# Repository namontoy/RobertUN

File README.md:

# RobertUN
Exploration Rover, inspired by the NASA's rovers that are exploring Mars. Developed at Universidad Nacional de Colombia - Sede Medellín, with the financial support from a research project.

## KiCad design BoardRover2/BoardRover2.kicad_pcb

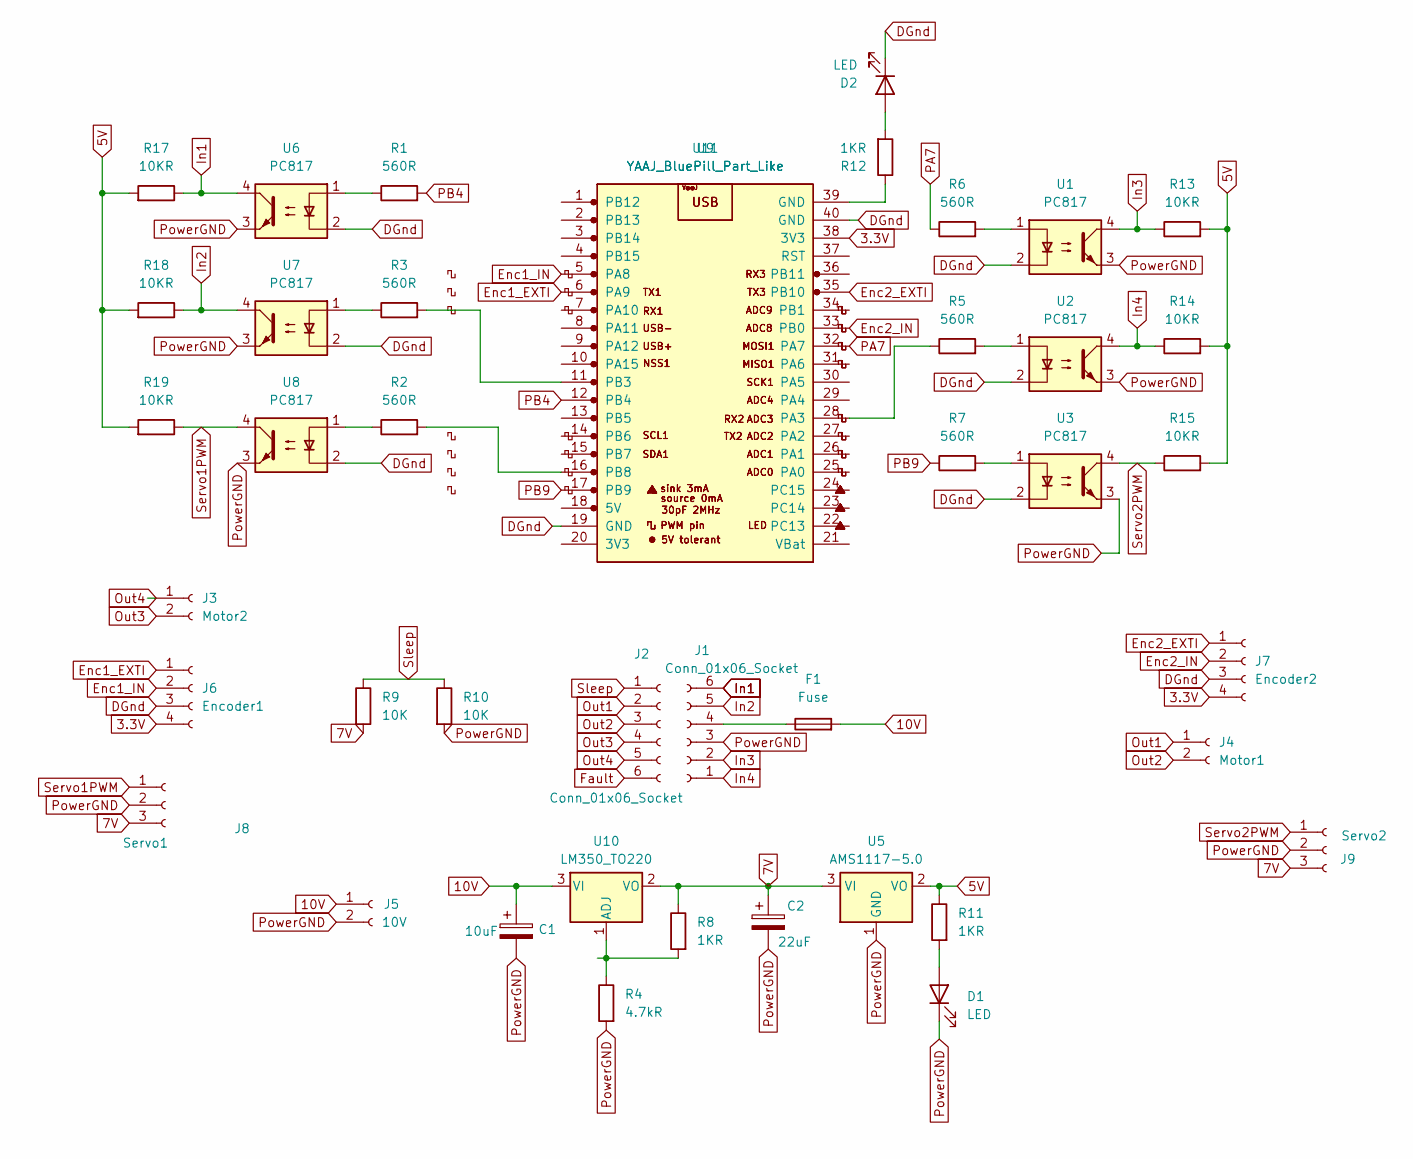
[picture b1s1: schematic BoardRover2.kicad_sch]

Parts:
C1: 10uF; C_1206_3216Metric
C2: 22uF; C_1206_3216Metric
D1, D2: LED; LED_D3.0mm_Clear
F1: Fuse; Fuse_1812_4532Metric
J1, J2: Conn_01x06_Socket; PinSocket_1x06_P2.54mm_Vertical
J3: Motor2; PhoenixContact_MSTBA_2,5_2-G-5,08_1x02_P5.08mm_Horizontal
J4: Motor1; PhoenixContact_MSTBA_2,5_2-G-5,08_1x02_P5.08mm_Horizontal
J5: 10V; PhoenixContact_MSTBA_2,5_2-G-5,08_1x02_P5.08mm_Horizontal
J6: Encoder1; JST_EH_S4B-EH_1x04_P2.50mm_Horizontal
J7: Encoder2; JST_EH_S4B-EH_1x04_P2.50mm_Horizontal
J8: Servo1; JST_EH_S3B-EH_1x03_P2.50mm_Horizontal
J9: Servo2; JST_EH_S3B-EH_1x03_P2.50mm_Horizontal
R1, R2, R3, R5, R6, R7: 560R; R_1206_3216Metric
R4: 4.7kR; R_1206_3216Metric
R8, R11, R12: 1KR; R_1206_3216Metric
R9, R10: 10K; R_1206_3216Metric
R13, R14, R15, R17, R18, R19: 10KR; R_1206_3216Metric
U1, U2, U3, U6, U7, U8: PC817; DIP-4_W7.62mm
U5: AMS1117-5.0; SOT-223-3_TabPin2
U9, U11: YAAJ_BluePill_Part_Like; PinSocket_1x20_P2.54mm_Vertical
U10: LM350_TO220; TO-220-3_Vertical

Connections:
3.3V: J6.4, J7.4, U11.38 (3V3)
5V: R11.1, R13.2, R14.2, R15.2, R17.2, R18.2, R19.2, U5.2 (VO)
7V: C2.1, J8.3, J9.3, R8.1, R9.2, U5.3 (VI), U10.2 (VO)
10V: C1.1, F1.2, J5.1, U10.3 (VI)
DGnd: D2.1 (K), J6.3, J7.3, U1.2, U2.2, U3.2, U6.2, U7.2, U8.2, U9.19 (GND), U11.40 (GND)
Enc1_EXTI: J6.1, U9.6 (PA9)
Enc1_IN: J6.2, U9.5 (PA8)
Enc2_EXTI: J7.1, U11.35 (PB10)
Enc2_IN: J7.2, U11.33 (PB0)
Fault: J2.6 (Fault)
In1: J1.6 (In1), R17.1, U6.4
In2: J1.5 (In2), R18.1, U7.4
In3: J1.2 (In3), R13.1, U1.4
In4: J1.1 (In4), R14.1, U2.4
unnamed: D1.2 (A), R11.2
unnamed: D2.2 (A), R12.2
unnamed: F1.1, J1.4 (MotorVCC)
unnamed: R1.1, U6.1
unnamed: R2.1, U8.1
unnamed: R3.1, U7.1
unnamed: R5.2, U2.1
unnamed: R6.2, U1.1
unnamed: R7.2, U3.1
unnamed: R12.1, U11.39 (GND)
unnamed: R3.2, U9.11 (PB3)
unnamed: R2.2, U9.16 (PB8)
unnamed: R4.1, R8.2, U10.1 (ADJ)
unnamed: R5.1, U11.28 (PA3)
Out1: J2.2 (Out1), J4.1
Out2: J2.3 (Out2), J4.2
Out3: J2.4 (Out3), J3.2
Out4: J2.5 (Out4), J3.1
PA7: R6.1, U11.32 (PA7)
PB4: R1.2, U9.12 (PB4)
PB9: R7.1, U9.17 (PB9)
PowerGND: C1.2, C2.2, D1.1 (K), J1.3 (MotorGND), J5.2, J8.2, J9.2, R4.2, R10.2, U1.3, U2.3, U3.3, U5.1 (GND), U6.3, U7.3, U8.3
Servo1PWM: J8.1, R19.1, U8.4
Servo2PWM: J9.1, R15.1, U3.4
Sleep: J2.1 (Sleep), R9.1, R10.1

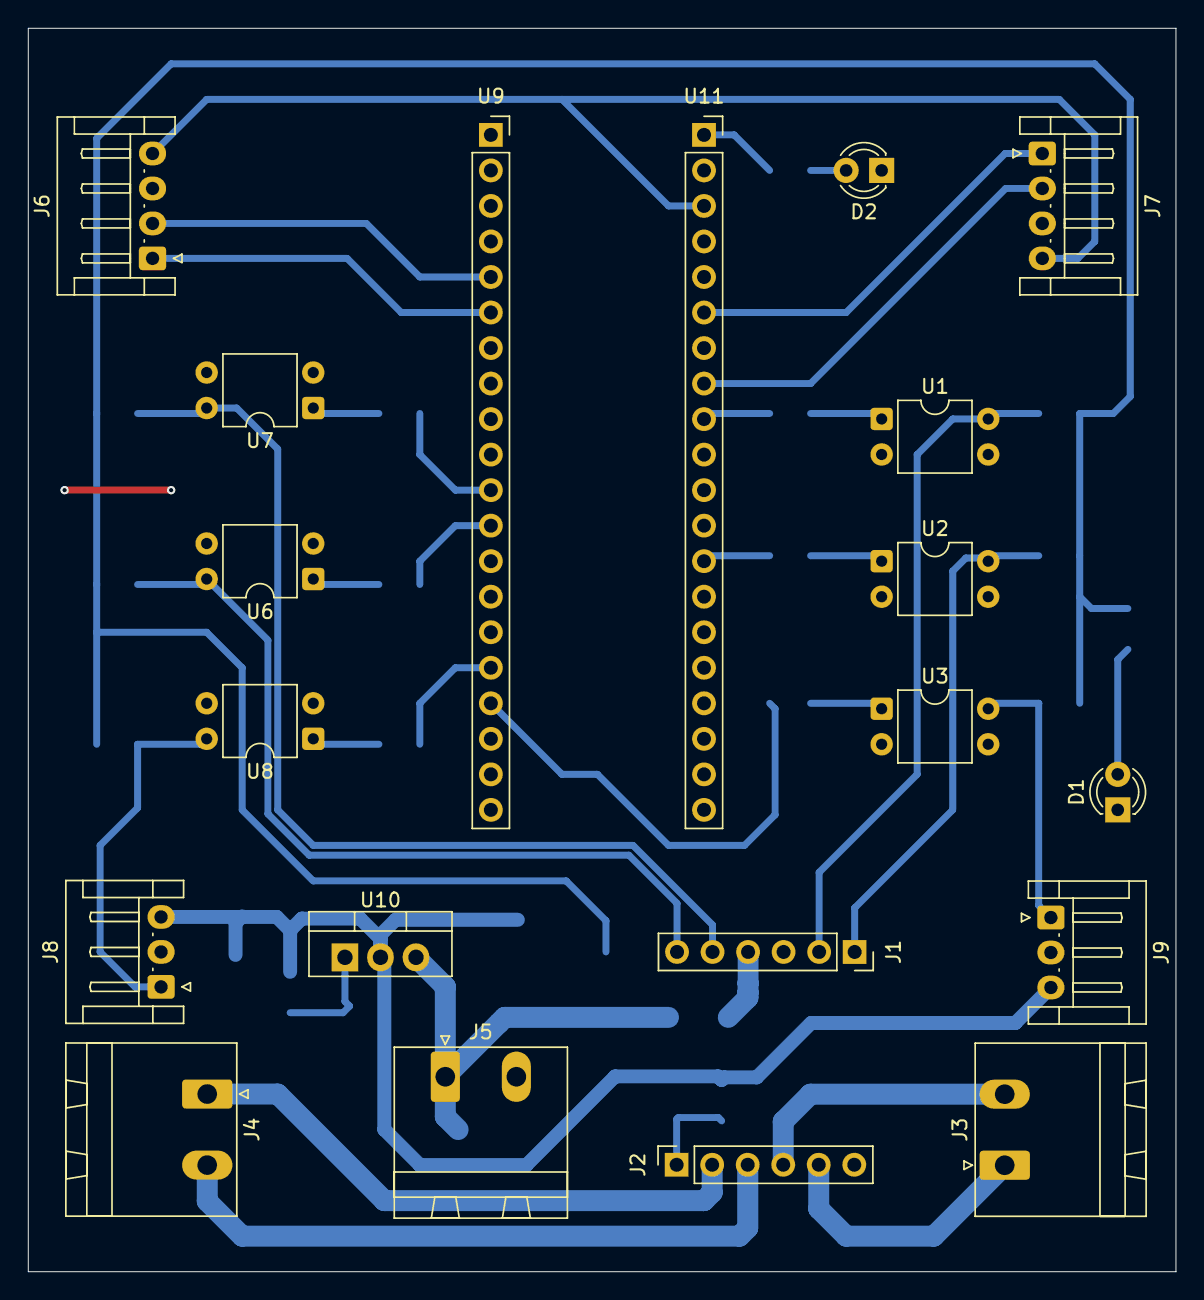
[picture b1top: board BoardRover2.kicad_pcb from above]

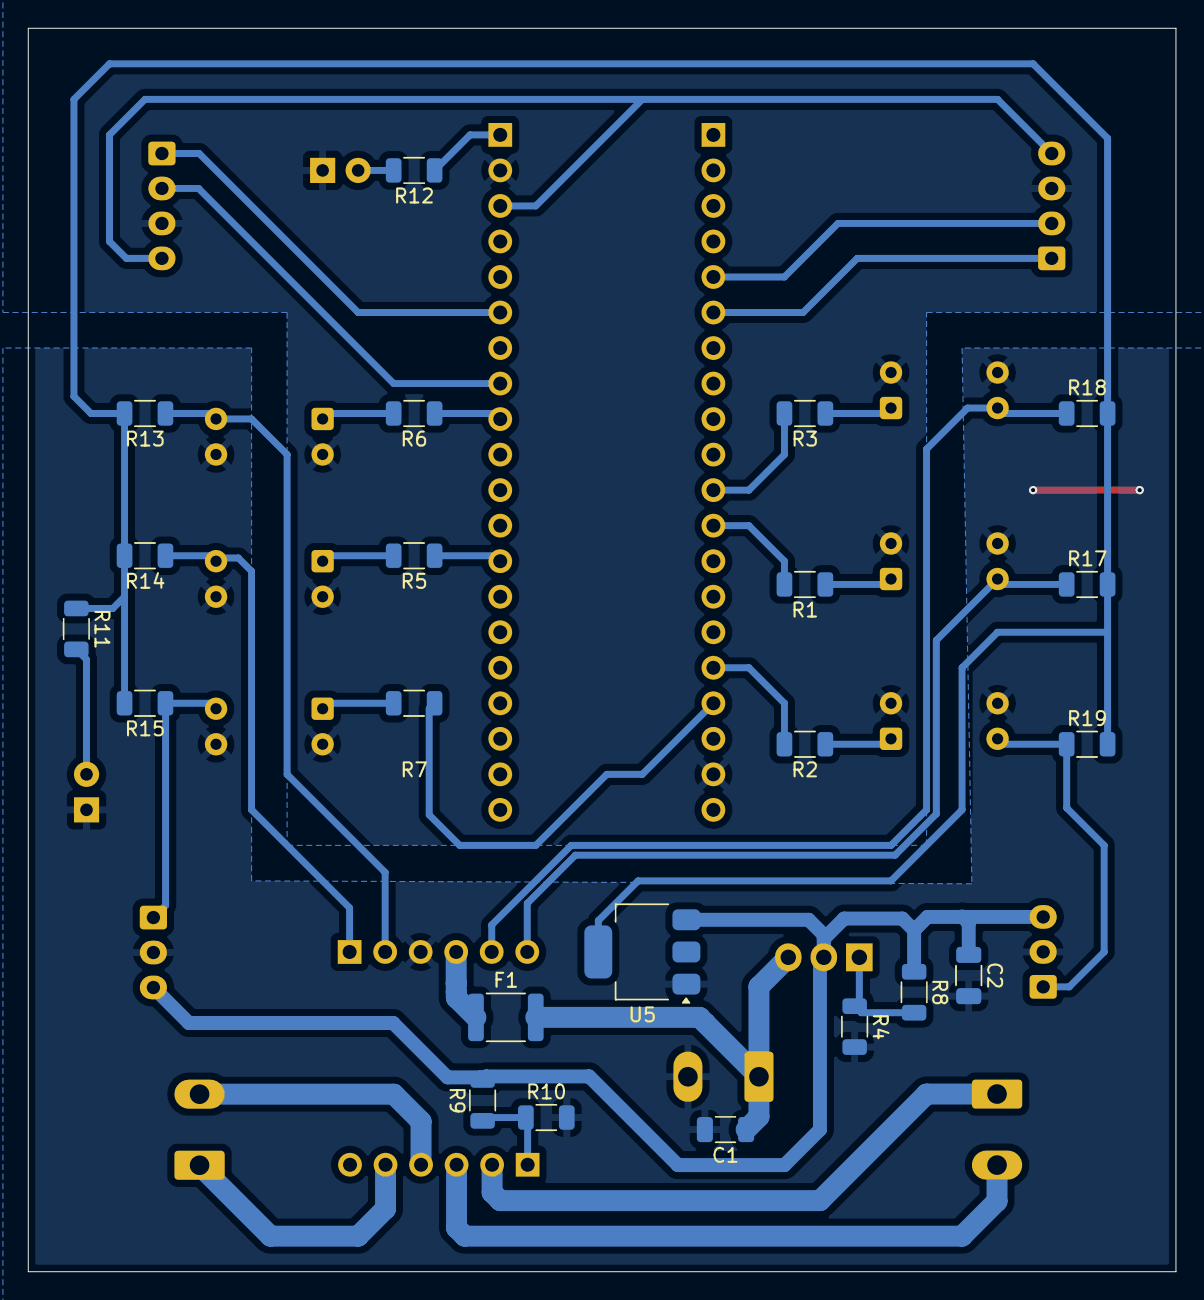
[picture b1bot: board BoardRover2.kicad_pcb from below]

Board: 2 copper layers, 82.1 x 88.9 mm, 42 parts (22 on the bottom side), 38 nets.

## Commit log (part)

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2025-11-19 Add files via upload - Jetson init
2025-11-19 add summary of additional programs used during Jetson Nano setup
2025-12-04 Create A_V dir and add Documentation
2025-12-04 Add install_yolo_deps.sh
2025-12-18 Board Kicad
2025-12-18 LED Y FUSIL
2025-12-18 revisado distancia pistas
2026-01-29 doble board y correxion
2026-02-14 info + storage bench
2026-02-14 creating a plan for the weeks
2026-02-17 Update2 plan.md
2026-02-21 ROS2 Humble setup + ros2_ws + /alive heartbeat node, also adding gitignore and checking docker install
2026-04-02 Add development environment context document for Dell, IsaacUN and Jetson setup
2026-04-02 Add initial development environment context - Dell laptop + Jetson setup (March 25, 2026)
2026-04-02 Add IsaacUN workstation configuration - Ubuntu 24.04, RTX 5080, ROS2 Jazzy, Isaac Sim 5.1.0 (March 30, 2026)
2026-04-02 Add CAN bus research document - Jetson Orin Nano hardware and software guide
2026-04-02 Network update - gigabit switch installed, static Ethernet IPs, DDS over wired (April 2, 2026)
2026-04-03 Add Dell laptop conda environments - ros2 (Humble) and ml (PyTorch+CUDA) configured (April 2, 2026)
2026-04-03 ZED 2i camera fully operational - USB 3.00 verified, depth pipeline confirmed (April 2, 2026)
2026-04-04 ZED 2i camera fully operational - USB 3.00 verified, ZED ROS2 Wrapper installed (April 3, 2026)
2026-04-04 Add ZED SDK headers to Dev Container for IntelliSense support
    - Install ZED SDK 5.2.2 headers-only in Dev Container (ubuntu22/cu12)
    - Fix permissions: chmod a+rX on /usr/local/zed and /usr/local/zed/include
    - IntelliSense now resolves sl::Camera, sl::Mat, sl::InitParameters etc.
    - Add Cyclone DDS loopback peer (127.0.0.1) to host and devcontainer configs
2026-04-04 Update project_context and new file about ZED2i - Jetson - ROS2 (April 3, 2026)
2026-04-06 Update project_context - updating CAN bus ideas - CANopen OSI Layer (April 5, 2026)
2026-04-08 Actualizando el archivo .gitignore
2026-04-08 Actualizando documentacion: carpeta de comandos utlizados en linx, carpeta con documentos de desarrollo de otros Rocker-Bogie, carpeta con imagens que sirven de guia
2026-04-12 Older changes - all in this commit: - Testing docker and how it works with ros2 - Creating a markdown that explains docker and how it was implemented - Week1.md for future implementations and roadmap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
2026-04-18 Add Docker helper menu scripts and Jetson Ethernet troubleshooting
2026-05-26 Add Xavier NX setup: JetPack 5.1.6, SATA SSD, llama.cpp LLM inference node
2026-05-29 Archivos relacionados con la tarjeta xavier para analizar cual es el mejor modelo
2026-05-29 actualizacion del context y agregando el log de comandos del trabajo realizado con la xavier
2026-05-29 context: document Isaac Sim ROS 2 bridge, snap removal, Docker migration (May 2026), also files about deep search for xavier
2026-05-30 First MVP for integration with images, ros2 and docker with mounts. Car test.
    Menu changes in docker helper for mounts workflow.
    Explaining problems with updates tools and dhcp errors for failed connections.
    Adding to the gitignore the images.
2026-05-30 Create a ROS2 color car count service. Request and response mode. Create a service contract using the srv file.
2026-06-20 (Minimal fix): Improving the red detection in the test using ros2 with detection workflows
